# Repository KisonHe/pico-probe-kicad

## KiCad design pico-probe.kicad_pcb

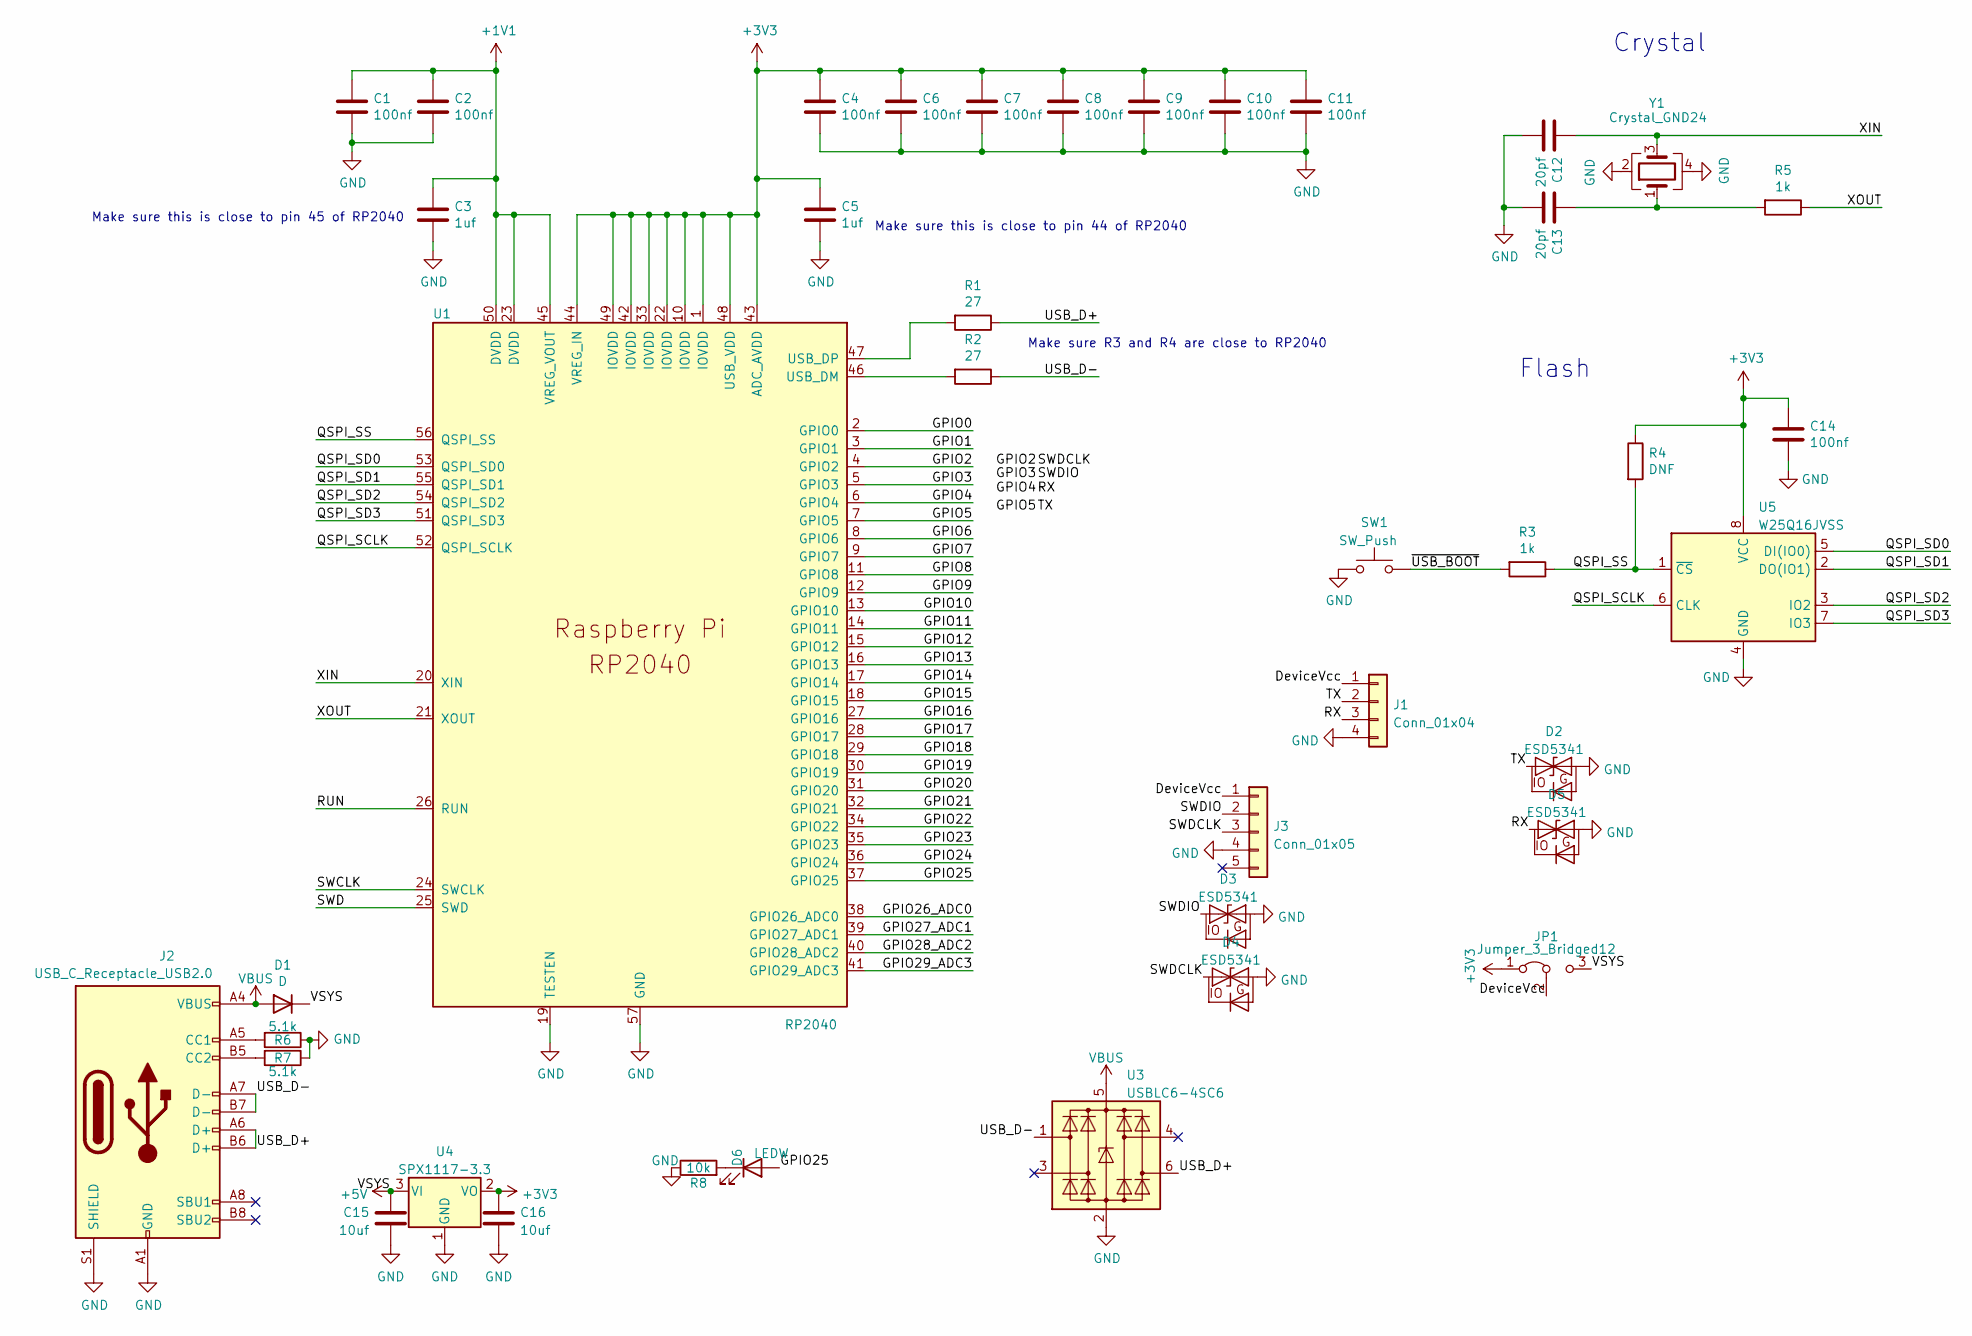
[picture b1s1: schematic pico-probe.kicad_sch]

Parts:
C1, C2, C4, C6, C7, C8, C9, C10, C11, C14: 100nf; C_0402_1005Metric; LCSC C307331
C3, C5: 1uf; C_0402_1005Metric; LCSC C52923
C12, C13: 20pf; C_0402_1005Metric; LCSC C1554
C15, C16: 10uf; C_0603_1608Metric; LCSC C19702
D1: D; C8678; LCSC C8678
D2, D3, D4, D5: ESD5341; esd5341; LCSC C239773
D6: LEDW; LED_0603_1608Metric; LCSC C2290
J1: Conn_01x04; PinHeader_1x04_P2.54mm_Vertical
J2: USB_C_Receptacle_USB2.0; USB_C_Receptacle_HRO_TYPE-C-31-M-12; LCSC C165948
J3: Conn_01x05; PinHeader_1x05_P2.54mm_Vertical
JP1: Jumper_3_Bridged12; PinHeader_1x03_P2.54mm_Vertical
R1, R2: 27; R_0402_1005Metric; LCSC C25190
R3, R5: 1k; R_0402_1005Metric; LCSC C11702
R4: DNF; R_0402_1005Metric
R6, R7: 5.1k; R_0402_1005Metric; LCSC C25905
R8: 10k; R_0402_1005Metric; LCSC C25744
SW1: SW_Push; SW_SPST_CK_RS282G05A3
U1: RP2040; RP2040-QFN-56
U3: USBLC6-4SC6; SOT-23-6
U4: SPX1117-3.3; SOT-223-3_TabPin2; LCSC C6862
U5: W25Q16JVSS; SOIC-8_5.23x5.23mm_P1.27mm
Y1: Crystal_GND24; C9002; LCSC C9002

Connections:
+1V1: C1.1, C2.1, C3.1, U1.23 (DVDD), U1.45 (VREG_VOUT), U1.50 (DVDD)
+3V3: C4.1, C5.1, C6.1, C7.1, C8.1, C9.1, C10.1, C11.1, C14.1, C16.1, JP1.1 (A), R4.1, U1.1 (IOVDD), U1.10 (IOVDD), U1.22 (IOVDD), U1.33 (IOVDD), U1.42 (IOVDD), U1.43 (ADC_AVDD), U1.44 (VREG_IN), U1.48 (USB_VDD), U1.49 (IOVDD), U4.2 (VO), U5.8 (VCC)
+5V: C15.1, D1.1 (K), JP1.3 (B), U4.3 (VI)
/DeviceVcc: J1.1, J3.1, JP1.2 (C)
/GPIO0: U1.2 (GPIO0)
/GPIO1: U1.3 (GPIO1)
/GPIO2: D4.1 (A1), J3.3, U1.4 (GPIO2)
/GPIO3: D3.1 (A1), J3.2, U1.5 (GPIO3)
/GPIO4: D5.1 (A1), J1.3, U1.6 (GPIO4)
/GPIO5: D2.1 (A1), J1.2, U1.7 (GPIO5)
/GPIO6: U1.8 (GPIO6)
/GPIO7: U1.9 (GPIO7)
/GPIO8: U1.11 (GPIO8)
/GPIO9: U1.12 (GPIO9)
/GPIO10: U1.13 (GPIO10)
/GPIO11: U1.14 (GPIO11)
/GPIO12: U1.15 (GPIO12)
/GPIO13: U1.16 (GPIO13)
/GPIO14: U1.17 (GPIO14)
/GPIO15: U1.18 (GPIO15)
/GPIO16: U1.27 (GPIO16)
/GPIO17: U1.28 (GPIO17)
/GPIO18: U1.29 (GPIO18)
/GPIO19: U1.30 (GPIO19)
/GPIO20: U1.31 (GPIO20)
/GPIO21: U1.32 (GPIO21)
/GPIO22: U1.34 (GPIO22)
/GPIO23: U1.35 (GPIO23)
/GPIO24: U1.36 (GPIO24)
/GPIO25: D6.2 (A), U1.37 (GPIO25)
/GPIO26_ADC0: U1.38 (GPIO26_ADC0)
/GPIO27_ADC1: U1.39 (GPIO27_ADC1)
/GPIO28_ADC2: U1.40 (GPIO28_ADC2)
/GPIO29_ADC3: U1.41 (GPIO29_ADC3)
/QSPI_SCLK: U1.52 (QSPI_SCLK), U5.6 (CLK)
/QSPI_SD0: U1.53 (QSPI_SD0), U5.5 (DI(IO0))
/QSPI_SD1: U1.55 (QSPI_SD1), U5.2 (DO(IO1))
/QSPI_SD2: U1.54 (QSPI_SD2), U5.3 (IO2)
/QSPI_SD3: U1.51 (QSPI_SD3), U5.7 (IO3)
/QSPI_SS: R3.1, R4.2, U1.56 (QSPI_SS), U5.1 (~CS)
/RUN: U1.26 (RUN)
/SWCLK: U1.24 (SWCLK)
/SWD: U1.25 (SWD)
/USB_D+: J2.A6 (D+), J2.B6 (D+), R1.1, U3.6 (I/O4)
/USB_D-: J2.A7 (D-), J2.B7 (D-), R2.1, U3.1 (I/O1)
/XIN: C12.1, U1.20 (XIN), Y1.3
/XOUT: R5.1, U1.21 (XOUT)
/~USB_BOOT: R3.2, SW1.2
GND: C1.2, C2.2, C3.2, C4.2, C5.2, C6.2, C7.2, C8.2, C9.2, C10.2, C11.2, C12.2, C13.2, C14.2, C15.2, C16.2, D2.2 (A2), D3.2 (A2), D4.2 (A2), D5.2 (A2), J1.4, J2.A1 (GND), J2.A12 (GND), J2.B1 (GND), J2.B12 (GND), J2.S1 (SHIELD), J3.4, R6.1, R7.1, R8.1, SW1.1, U1.19 (TESTEN), U1.57 (GND), U3.2 (GND), U4.1 (GND), U5.4 (GND), Y1.2, Y1.4
unnamed: C13.1, R5.2, Y1.1
unnamed: D6.1 (K), R8.2
unnamed: J2.A5 (CC1), R6.2
unnamed: J2.B5 (CC2), R7.2
unnamed: R1.2, U1.47 (USB_DP)
unnamed: R2.2, U1.46 (USB_DM)
VBUS: D1.2 (A), J2.A4 (VBUS), J2.A9 (VBUS), J2.B4 (VBUS), J2.B9 (VBUS), U3.5 (VBUS)

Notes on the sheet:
Crystal
Make sure this is close to pin 45 of RP2040
Flash
Make sure R3 and R4 are close to RP2040
Make sure this is close to pin 44 of RP2040

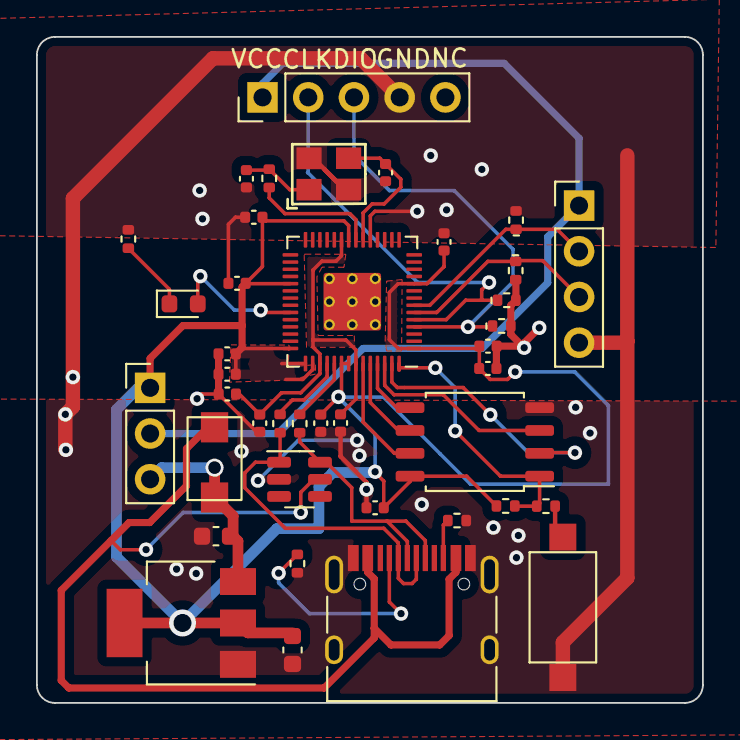
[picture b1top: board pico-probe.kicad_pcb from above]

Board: 2 copper layers, 37.0 x 37.0 mm, 40 parts (0 on the bottom side), 28 nets.

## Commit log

2023-02-12 V0.0.1 sch down
2023-02-12 添加LED
